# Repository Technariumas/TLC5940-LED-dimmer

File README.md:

# TLC5940-LED-dimmer
16 channel 12bit PWM dimmer with RS485 interface based on Arduino and TLC5940. Also available on [Tindie](https://www.tindie.com/products/miceuz/16-channel-12-bit-pwm-led-dimmer/)

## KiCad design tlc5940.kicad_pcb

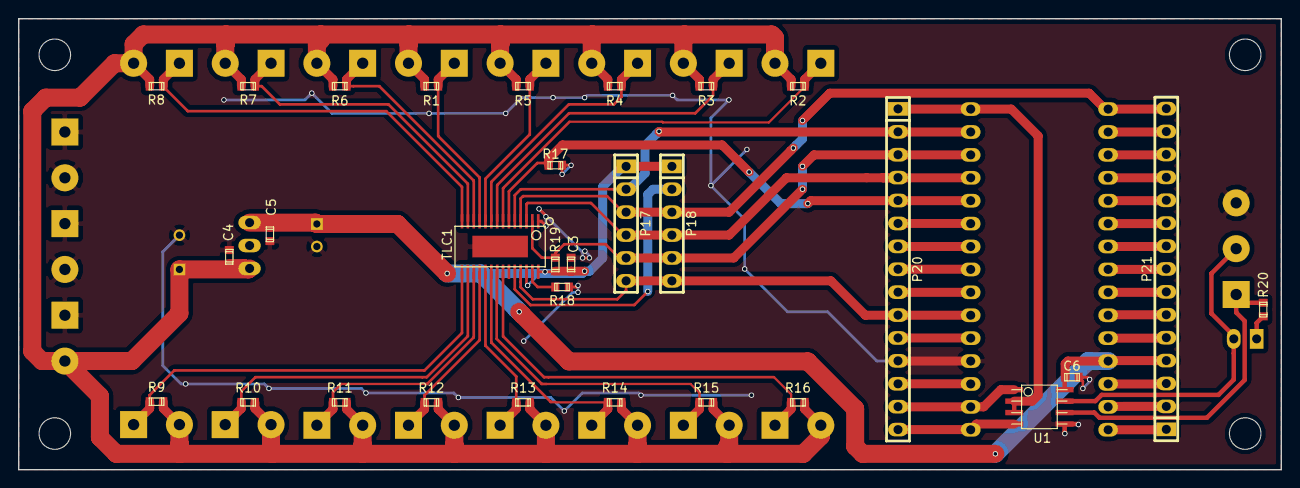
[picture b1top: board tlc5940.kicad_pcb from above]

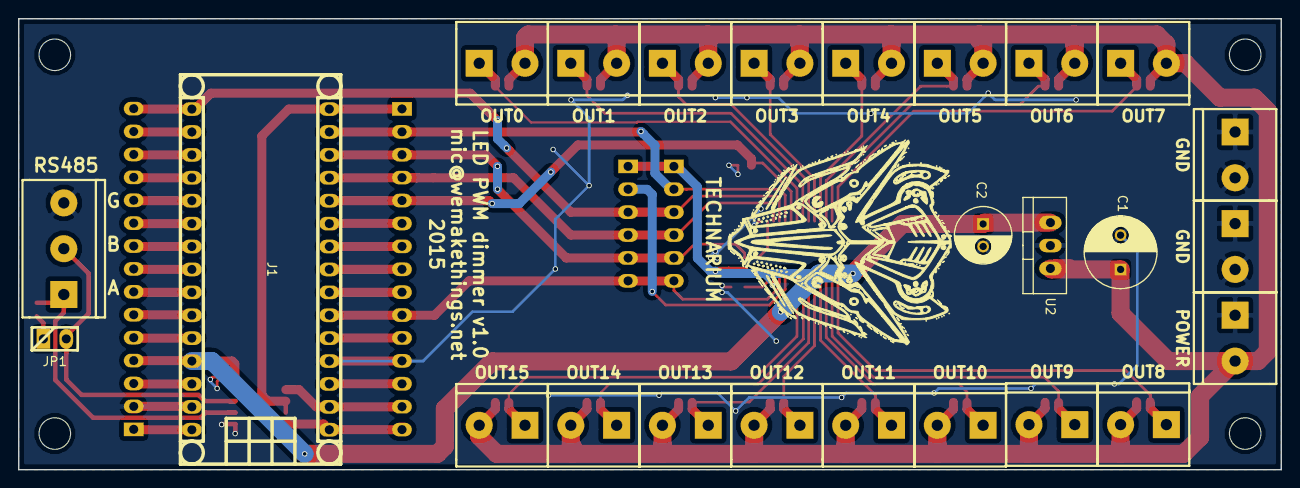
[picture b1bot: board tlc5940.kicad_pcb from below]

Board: 2 copper layers, 140.0 x 50.0 mm, 55 parts (25 on the bottom side), 51 nets.

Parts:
C1: 470u; C_Radial_D8_L13_P3.8
C2: 470u; C_Radial_D6.3_L11.2_P2.5
C3, C4, C5, C6: 1u; c_0603
J1: Arduino_Nano_Header; arduino_nano_header
JP1: TERM; pin_strip_2
P1: OUT0; mors_2p
P2: OUT1; mors_2p
P3: OUT2; mors_2p
P4: OUT3; mors_2p
P5: OUT4; mors_2p
P6: OUT5; mors_2p
P7: OUT6; mors_2p
P8: OUT7; mors_2p
P9: OUT8; mors_2p
P10: OUT9; mors_2p
P11: OUT10; mors_2p
P12: OUT11; mors_2p
P13: OUT12; mors_2p
P14: OUT13; mors_2p
P15: OUT14; mors_2p
P16: OUT15; mors_2p
P17, P18: CONN_01X06; pin_strip_6
P19: POWER; mors_2p
P20, P21: CONN_01X15; pin_strip_15
P22: B RS485 A; mors_3p
P1020, P1021: GND; mors_2p
R1, R2, R3, R4, R5, R6, R7, R8, R9, R10, R11, R12, R13, R14, R15, R16, R17, R19: R; r_0603
R18: 324; r_0603
R20: 120; r_0603
TLC1: TLC5940-TSSOP; HTSSOP-28
U1: SP3481CN; so-8
U2: 7805; TO-220_Bipolar-BCE_Vertical

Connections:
+5V: C2.1, C3.1, C5.1, C6.1, J1.27, P17.1, P18.1, P21.4, R19.1, TLC1.26, TLC1.28, U1.8, U2.3
+12V: C1.1, C4.1, P1.2, P2.2, P3.2, P4.2, P5.2, P6.2, P7.2, P8.2, P9.2, P10.2, P11.2, P12.2, P13.2, P14.2, P15.2, P16.2, P19.2, R1.1, R2.1, R3.1, R4.1, R5.1, R6.1, R7.1, R8.1, R9.1, R10.1, R11.1, R12.1, R13.1, R14.1, R15.1, R16.1, U2.1
/BLANK: J1.13, P17.5, P18.5, P20.3, R19.2, TLC1.2
/GSCLK: J1.6, P17.6, P18.6, P20.10, TLC1.25
/SCLK: J1.16, P17.3, P18.3, P21.15, TLC1.4
/SIN: J1.14, P17.2, P20.2, TLC1.5
/VPRG: J1.11, P20.5, R17.2, TLC1.6
/XLAT: J1.12, P17.4, P18.4, P20.4, TLC1.3
GND: C1.2, C2.2, C3.2, C4.2, C5.2, C6.2, J1.4, J1.29, P19.1, P20.12, P21.2, P22.3, P1020.1, P1020.2, P1021.1, P1021.2, R17.1, R18.2, TLC1.1, TLC1.29, U1.5, U2.2
unnamed: J1.1, P20.15, U1.4
unnamed: J1.2, P20.14, U1.1
unnamed: J1.3, P20.13
unnamed: J1.5, P20.11
unnamed: J1.7, P20.9
unnamed: J1.8, P20.8
unnamed: J1.9, P20.7
unnamed: J1.10, P20.6
unnamed: J1.15, P20.1, U1.2, U1.3
unnamed: J1.17, P21.14
unnamed: J1.18, P21.13
unnamed: J1.19, P21.12
unnamed: J1.20, P21.11
unnamed: J1.21, P21.10
unnamed: J1.22, P21.9
unnamed: J1.23, P21.8
unnamed: J1.24, P21.7
unnamed: J1.25, P21.6
unnamed: J1.26, P21.5
unnamed: J1.28, P21.3
unnamed: J1.30, P21.1
unnamed: JP1.1, R20.2
unnamed: JP1.2, P22.2, U1.7
unnamed: P1.1, R2.2, TLC1.7
unnamed: P2.1, R3.2, TLC1.8
unnamed: P3.1, R4.2, TLC1.9
unnamed: P4.1, R5.2, TLC1.10
unnamed: P5.1, R1.2, TLC1.11
unnamed: P6.1, R6.2, TLC1.12
unnamed: P7.1, R7.2, TLC1.13
unnamed: P8.1, R8.2, TLC1.14
unnamed: P9.1, R9.2, TLC1.15
unnamed: P10.1, R10.2, TLC1.16
unnamed: P11.1, R11.2, TLC1.17
unnamed: P12.1, R12.2, TLC1.18
unnamed: P13.1, R13.2, TLC1.19
unnamed: P14.1, R14.2, TLC1.20
unnamed: P15.1, R15.2, TLC1.21
unnamed: P16.1, R16.2, TLC1.22
unnamed: P18.2, TLC1.24
unnamed: P22.1, R20.1, U1.6
unnamed: R18.1, TLC1.27

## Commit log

2015-10-25 Initial
2017-12-17 Add some shameless marketing and a pic
